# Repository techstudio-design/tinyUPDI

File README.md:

## What is *tinyUPDI*?

The ***tinyUPDI*** is a tiny programmer uses for programming *any* AVR that supports SerialUPDI interface. Unlike other UPDI programmers, it only requires one USB port and automatically switches between UPDI programming and debugging serial mode.

## Why did you make it?

Many modern AVR developers in the past, we included, hacks together a USB Serial adaptor with a few components 
together 
for programming UPDI-capable AVR chips. Those hacks work as a UPDI programmer, it is however in reality often 
requires another USB/UART 
ports for serial debugging printout.  The *tinyUPDI* 
supports automatic switch 
between UPDI and UART interfaces via a single USB port, saving the needs for connecting two USB ports.

## What makes it special?

- Single USB port connection supports both UPDI and debugging Serial Monitor
- Supports all UPDI-programmable AVRs
- Supports Arduino IDE and PlatformIo development envrionment
- Works with multiple Arduino Cores such as [megaTinyCore](https://github.com/SpenceKonde/megaTinyCore), [DxCore](https://github.com/SpenceKonde/DxCore) and should  [MegaCoreX](https://github.com/MCUdude/MegaCoreX)
- Based on latest [CP2101N](https://www.silabs.com/documents/public/data-sheets/CP2101.pdf) from Silicon lab.
- No USB driver required for macOS, Windows and Linux (kernel v2.6.12 onward)
- Capable of powering target board (5v only) directly via the 6-pin programming header from USB power source

## Working with megaTinyCore/DxCore

### Arduino IDE

Instead of using the SerialUPDI implementation `pymcuprog.py` from Microchip, megaTinyCore/DxCore ships with its own version of SerialUPDI, When working with Arduino IDE, any of the SerialUPDI options in *Tools -> Programmers* would *work* with *tinyUPDI*. However, when using modes higher than 230400bps, it occasionally failed or in the case of running at  921600bps, the underneath programming function failed to read the data correctly and will fallback to 115200bps. We recommend to use the options for baudrate of 230400bps for the best performance between speed and reliablity.

#### Arduino IDE with Apple Silicon

The tinyUPDI works well under the Windows, Linux and MacOS in general. However, when using it with MacOS Apple Silicon machines, it does not output data to the Serial Monitor of Arduino IDE for some unknown reason. One workaround is to use an external terminal software such as [CoolTerm]([CoolTerm - Download](https://coolterm.en.lo4d.com/windows) where DTR state can be set, this works but is not seemless as you would need to disconnect the terminal before the programming.

Another altertive is to use PlatformIO as your IDE environment which provide better user experience between progamming mode and serial debugging mode. 

### PlatformIO

*tinyUPDI* works well under PlatformIO with megaTinyCore with proper configuration. 

#### Install pymcuprog

The build-in programmer that is tightly integreated with megaTinyCore and works well with Arduino IDE, but not with PlatformIO. We recommend to 
download and install the [pymcuprog](https://pypi.org/project/pymcuprog/) from Microchip.

#### Configure PlatformIO.ini

Here is an example of `platformio.ini` configuration for running an Attiny3227 at 20MHz on a MacOS:

```
[env:ATtiny3227]
board = ATtiny3227
platform = atmelmegaavr
framework = arduino
board_build.f_cpu = 20000000L
monitor_speed = 115200
monitor_rts = 0

upload_protocol = custom
upload_port = /dev/cu.usbserial* ; for MacOS
upload_speed = 230400

; for using pymcuprog, download and install it via PyPi
upload_flags =
    --tool
    uart
    --device
    $BOARD
    --uart
    $UPLOAD_PORT
    --clk
    $UPLOAD_SPEED
upload_command = pymcuprog write --erase $UPLOAD_FLAGS --filename $SOURCE
```

The `monitor_rts = 0` flag is only required when operating under MacOS with Apple Silicon, it ensures the terminal would activated upon opening 
correctly.

## Working with MegaCoreX

Unfortunately at this moment, we don't have any MCU chip/board running with MegaCoreX with us to test the tinyUPDI 
but we think it very likely should work without any extra issue other than what we covered here. We will provide 
an update of this section once we have the chance to test it.

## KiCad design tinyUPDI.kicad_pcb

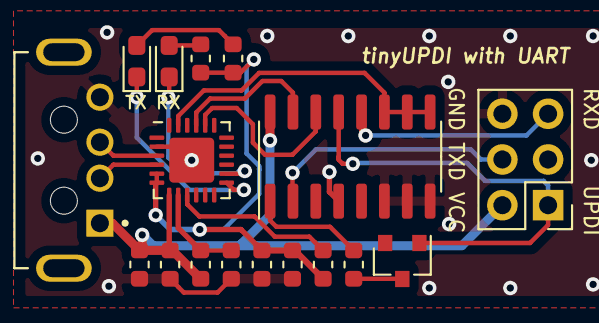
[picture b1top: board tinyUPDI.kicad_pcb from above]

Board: 2 copper layers, 17 parts (0 on the bottom side), 19 nets.

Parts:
C1, C4: 4.7uF; C_0603_1608Metric
C2, C3: 100nF; C_0603_1608Metric
D1: TXD/GREEN; LED_0603_1608Metric_Pad1.05x0.95mm_HandSolder
D2: RXD/YELLOW; LED_0603_1608Metric_Pad1.05x0.95mm_HandSolder
D3: BAT54; SOT-23
J1: USB_A; USB-05_without_extend_silkscreen
J2: Conn_02x03_Odd_Even; PinHeader_2x03_P2.54mm_Vertical
R1, R3, R5, R6: 1k; R_0603_1608Metric
R2: 22k; R_0603_1608Metric
R4: 47k; R_0603_1608Metric
U1: CP2102N-A01-GQFN24; QFN-24-1EP_4x4mm_P0.5mm_EP2.5x2.5mm
U2: 74HC4053D; SOIC-16_3.9x9.9mm_P1.27mm

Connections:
+3V3: C1.1, C3.1, R1.1, R3.1, R5.1, U1.5, U1.6
GND: C1.2, C2.2, C3.2, C4.2, J1.4, J2.6, R4.2, U1.2, U1.25, U2.4, U2.6, U2.7, U2.8
unnamed: D1.2, R1.2
unnamed: D2.2, R3.2
unnamed: D3.3, R6.2
unnamed: J1.2, U1.4
unnamed: J1.3, U1.3
unnamed: R2.2, R4.1, U1.8
unnamed: R5.2, U1.9
unnamed: R6.1, U2.1
unnamed: U1.20, U2.14
unnamed: U1.21, U2.15
unnamed: U1.23, U2.9, U2.10, U2.11
RXD: J2.5, U2.12
RXT: D1.1, U1.13
TXD: J2.4, U2.2
TXT: D2.1, U1.14
UPDI: D3.1, J2.1, U2.13
VBUS: C2.1, C4.1, J1.1, J2.2, R2.1, U1.7, U2.16

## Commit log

2023-03-05 add tinyUPDI image
2023-03-05 slight changes in README writeup
2023-03-05 change wording regarding MegaCoreX
2023-03-05 title and subtitles alignment of README
2023-03-05 wording, typo corrections of README

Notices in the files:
tinyUPDI.kicad_pcb:
Copyright - Tech Studio Design LLP, 2022
